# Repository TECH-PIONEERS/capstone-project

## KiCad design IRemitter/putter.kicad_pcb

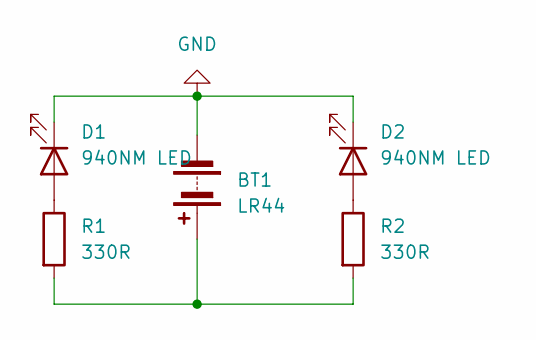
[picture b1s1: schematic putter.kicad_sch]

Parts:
BT1: LR44; batt holder
D1, D2: 940NM LED; LED_D5.0mm
R1, R2: 330R; R_Axial_DIN0207_L6.3mm_D2.5mm_P7.62mm_Horizontal

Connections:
GND: BT1.2 (-), D1.1 (K), D2.1 (K)
unnamed: BT1.1 (+), R1.2, R2.2
unnamed: D1.2 (A), R1.1
unnamed: D2.2 (A), R2.1

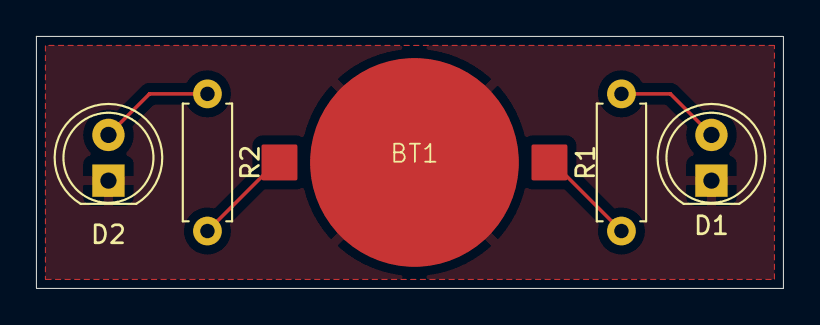
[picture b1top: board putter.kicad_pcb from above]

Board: 2 copper layers, 41.5 x 14.0 mm, 5 parts (0 on the bottom side), 4 nets.

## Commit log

2024-01-23 docs : 240109 회의록
2024-02-07 240116 회의록 - 류지수
2024-02-07 docs : 240123 회의록 - 구민성
2024-02-07 docs : 240130 회의록 - 한예지
2024-02-07 docs : 240116 회의록 - 류지수
2024-02-07 docs:주제 신청서 1차자료
2024-02-08 docs : 240207 회의록 - 박주미
2024-02-08 docs : 주제 신청 1차
2024-02-14 docs : 240214 회의록 - 류지수
2024-02-16 docs : 240216 회의록 - 박주미
2024-02-18 docs : 주제 신청 2차
2024-02-19 docs : 주제 신청 3차
2024-02-23 docs : 240222 회의록 - 류지수
2024-02-24 docs : 주제 신청 4차
2024-02-25 docs : 주제 신청 5차
2024-02-26 docs : 240225 회의록 - 박주미
2024-02-26 docs : 주제 신청 6차
2024-02-26 docs : 240226 회의록 - 한예지
2024-02-27 docs : 주제 신청 7차
2024-02-28 docs : 장애물 알림 장치 2차, 3차 신청본 삭제
2024-02-28 docs : 주제 신청 8차
2024-02-28 docs : 주제 신청 최종
2024-03-03 docs : 안전한 야간 주행을 위한 자전거, 킥보드 시스템 1차 작성
2024-03-05 docs : 시각 장애인을 위한 골프 서비스 1차 작성
2024-03-05 docs : 시각장애인을 위한 골프 시스템 1차 계획서 작성
2024-03-05 docs : 시각장애인을 위한 골프 서비스 1차 수정본
2024-03-05 docs : 공과헤드정렬
2024-03-05 docs : 공과헤드정렬 제출
2024-03-05 docs : 공과 헤드 정렬 계획서 최종본
2024-03-05 docs : 공과 헤드 정렬 계획서 최종
2024-03-05 docs : 사운드 골핑 최종
2024-03-10 docs : 퍼팅서포터 주제 신청
2024-03-10 docs : 퍼팅서포터 주제 신청서
2024-03-10 docs : [tech-pioneers]-주제 선정 보고서
2024-03-16 docs : 퍼팅서포터 주제 선정 보고서
2024-03-25 feat: 컬러 기반 공 추적 및 Canny Edge 알고리즘 결합 - 수정 필요
2024-03-25 test
2024-03-25 fix : colorLower 값 수정
2024-03-25 feat: pyttsx3, gTTS 사용 TTS 함수
2024-03-27 add : findball 주석 추가
2024-03-27 test : HoughCircles 추가해 원 검출 판별
2024-03-27 test : CannyEdge 추가
2024-03-27 comment : 할 일 추가
2024-03-27 feat : Canny Edge 추가
2024-04-01 fix : break 삭제
2024-04-01 fix : golfball_size 변수 추가
2024-04-01 fix : ZeroDivisionError 해결
2024-04-01 feat: network camera connect
2024-04-01 feat: 비프음 출력 함수를 쓰레드로 구현 및 테스트 완료
2024-04-09 바닥판 디렉토리 생성
2024-04-17 feat: crop video and add fucn(1px to 1mm)
2024-04-17 feat: add 수선의 발 코드
2024-05-01 feat: camera calibration
2024-05-01 feat: test-camera picamera connect
2024-05-01 feat: image
2024-05-01 feat: image2
2024-05-01 refact: camera
2024-05-01 카메라 보정 함수와 find ball 코드 합침
2024-05-01 카메라 보정 함수와 find ball 코드 합친 버전
2024-05-01 Picamera1 사용 버전 코드
2024-05-03 ball tracking with picamera
2024-05-03 Picamera v1 삭제
2024-05-03 feat: 공 외곽선이 특정 범위 벗어났을 경우 경고 문구 출력하는 코드
2024-05-03 add : IR pyserial test
2024-05-03 add : ir_result.txt
2024-05-03 feat: 공 외곽선이 특정 범위 벗어났을 경우 경고 문구와 비프음 출력하는 코드
2024-05-03 feat: findball + range detection + beep sound
2024-05-06 코드 파일 정리
2024-05-06 add : ir sensor with circle
2024-05-06 ir draw code
2024-05-06 feat: 골프공 검출
2024-05-06 add code
2024-05-06 feat: 골프공 검출 관련 코드
2024-05-06 Create ir_test_0506_2
    적외선 거리 측정을 탄젠트로 하는 코드 추가 버전
2024-05-06 yellow range changed
2024-05-06 fix : colorLower change
2024-05-06 add : goal code
2024-05-06 add : 골과 공 정렬
2024-05-06 feat: ballOutOfRangeAlert 함수에 isBallOutOfRang flag 추가
2024-05-07 add : get goal position
2024-05-08 refactor & add picam fps setting
2024-05-09 add : calibration
2024-05-09 카메라 보정 값
2024-05-09 ir draw test
2024-05-09 docs : 중간 발표 ppt
2024-05-09 docs : 중간 발표 ppt 수정
2024-05-11 findball code
2024-05-11 add : ir - findball mapping
2024-05-11 add : ir test 0511
2024-05-11 add: scale value func
2024-05-11 add : is_vaid_string
2024-05-11 add: min max value
2024-05-11 add : ir-opencv mapping
2024-05-13 feat: IR Camera1, 2를 서로 평행한 위치에 배치하여 퍼터의 가운데에 부착된 LED로 정렬 판단하는 코드
2024-05-13 feat: mapping_thread.py에 main 함수 추가
2024-05-13 feat: mapping_thread.py 원본
2024-05-13 feat: multiProcess
2024-05-13 jisu mapping
2024-05-13 feat: mapping_multiprocessing
2024-05-13 todo: multiprocessing
2024-05-14 add : mapping serial baudrate, timeout
2024-05-14 Update IRCamera.ino
    add more delay and reduced baudrate
2024-05-14 Create IRCameraBack
2024-05-14 Update IRCameraBack
2024-05-14 feat: utils pagame 수정
2024-05-14 add: calculate ball degrees
2024-05-14 add : is_valid_string
2024-05-14 add : 공 방향 전환 알고리즘
2024-05-14 add :utils is_valid_string
2024-05-14 del : unused
2024-05-14 mapping-0514-jisu
2024-05-14 fix : renaming mapping-0514.py
2024-05-14 add: 방향 코드
2024-05-14 add : ball direction
2024-05-16 add : calibration img
2024-05-16 camera calibration 값 수정(v5)
2024-05-16 add : image3
2024-05-16 camera calibration 값 수정(v6)
2024-05-16 utils 함수 수정: camera calibration 값 설정(v6)
2024-05-16 fix : circle, add calibration
2024-05-16 feat: Picam에서 BGR 출력 코드
2024-05-17 add : 5월 3주차 중간 점검 발표 자료
2024-05-17 5월 3주차 중간 점검 영상 수정
2024-05-17 feat: Picam에서 BGR 출력 코드 수정
2024-05-17 delete: HW 고정되기 이전에 수집한 Calibration 이미지들 삭제
2024-05-17 feat: TTS를 멀티 프로세스로 수행하는 코드 파일 mapping-p3-tts.py, utilsp3.py
2024-05-18 mapping code
2024-05-18 fix : utils 1023 delete
2024-05-18 IR Camera mapping
2024-05-18 add : gitignore
2024-05-18 docs: change file path
2024-05-18 add: gitignore
2024-05-18 feat: mapping-hard.py에 tts process 추가한 mapping-hard-tts.py 코드 파일
2024-05-18 TTS: 퍼터 값이 없을 경우 경고 알림
2024-05-18 mapping
2024-05-18 feat: checkt ball movement
2024-05-18 tts_flag 추가
2024-05-18 mapping-hard
2024-05-18 feat: tts manager
2024-05-18 feat: multiprocessing global variable list solved
2024-05-20 feat: multiprocessing manager 수정
2024-05-20 multiprocessing manager namespace
2024-05-20 feat: tts & jisu code 합침
2024-05-20 feat: change ball color to red
2024-05-20 multiprocessing
2024-05-20 feat: tts connect
2024-05-20 add: 헤드와 공 거리 함수 추가
2024-05-20 add : pixel to cm connect
2024-05-21 pylirc 파일
2024-05-21 add : 에지 검출 코드
2024-05-21 add: tts fix
2024-05-21 feat: fix ball_align bottom up return
2024-05-21 sound mid_beep 추가
2024-05-21 feat: add isMoving when calculate distance ball from head
2024-05-21 검은색만 마스킹
2024-05-21 feat: add import utils
2024-05-21 beep sound 추가
2024-05-21 feat: subprocess remote 코드 추가
2024-05-22 feat: remote process
2024-05-22 feat: head turn -ing
2024-05-23 feat: generate_TTS(text) 함수 추가
2024-05-23 English voice test
2024-05-23 feat: head alin
2024-05-24 add : 5월 4주차 중간 발표자료
2024-05-24 head align -ing
2024-05-24 add : 5월 4주차 중간 발표자료 수정
2024-05-24 fix : find code & utils tts 소리 변경
2024-05-24 feat: add confition
2024-05-24 ir align
2024-05-24 feat: add tts
2024-05-24 up down sound
2024-05-24 얼라인먼트 코드 업데이트
2024-05-24 얼라인먼트 업데이트
2024-05-24 code change
2024-05-24 안 쓰는 파일들 삭제
2024-05-24 head align
2024-05-24 first test code
2024-05-24 add : sound half version
2024-05-27 value_lock_code: tts_flag가 Value & Lock 사용하도록 수정한 코드
2024-05-28 request from jisu-R
2024-05-29 tts_flag -ing
2024-05-29 refactor: test_final_code
2024-05-30 feat: 공위치가 헤드 범위 밖으로 가면 경고 문구 출력하는 함수 -ing
2024-05-30 fix: order
2024-05-30 create directory IR_Asynchronous
2024-05-30 fix: order problem
2024-05-30 add : 5월 5주차 중간 발표 자료
2024-05-31 fix : pygame.mixer path error
2024-05-31 ball_shot
2024-05-31 goal
2024-05-31 refactor: distance func
2024-05-31 feat: 정렬 이후 동작 추가
2024-05-31 todo: ir y
2024-05-31 todo: ir y align
2024-06-01 refactor: 파일 구조
2024-06-01 add: dist direction
2024-06-01 fix: ball missing
2024-06-01 fix : head down , up female voice
2024-06-01 feat: change tts voice
2024-06-01 fix: 골 쳤을 때 판단
2024-06-01 fix: shot
2024-06-01 feat: 공 슛 조건 추가
2024-06-01 MSG file add
2024-06-01 update MSG
2024-06-01 feat: head position align
2024-06-01 head align beep case
2024-06-01 del: comment
2024-06-01 asdf
2024-06-01 head align case add
2024-06-01 align y axis
2024-06-01 add : lose, nice shot beep sound
2024-06-01 refactor: del comment and unused func
2024-06-01 add beep source
2024-06-01 feat: head align 기울기 sleep time 적용
2024-06-01 fix: priority problem
2024-06-01 add: cw ccw tts
2024-06-01 fix: distance
2024-06-01 add condition
2024-06-01 fix : voice once
2024-06-01 feat: test_head_align 함수 수정
2024-06-01 final code, final_code_v1
2024-06-01 todo: fix goal & wall crush case
2024-06-03 fix: tts_process add condition about shot_flag
2024-06-03 fix: goal tts
2024-06-03 docs: organize files
2024-06-03 feat: final.pt
2024-06-03 goal_x, goal_y 반경 값 정확하게 변경
2024-06-03 feat: 홀 안에서 방향이 바뀌는 경우를 위한 함수 수정
2024-06-04 fix : goal_x, goal_y 수정
2024-06-04 fix : goal_x, goal_y, x_threshold, y_threshold complete
2024-06-04 test : only straight goal
2024-06-04 fix : goal_x, y, xy threahold rollback, wall crash threshold 2.5
2024-06-04 fix : stuck on the threshold resolved
2024-06-04 fix: timer
2024-06-04 add : is_direction_chagned value
2024-06-04 feat:벽 범위에 있는 지 판단하는 코드 추가
2024-06-04 add: out of range tts
2024-06-04 feat: return_ball_direction
2024-06-04 todo: wall crush problem
2024-06-05 ball hit wall case -ing
2024-06-05 feat: temp_return_ball_direction 수정
2024-06-05 hole
2024-06-05 fix : check_movement arg
2024-06-05 공이 끝 벽에 맞고 홀로 들어오는 경우를 위해 uw 추가
2024-06-05 fix : check_movement threshold to shot_threshold
2024-06-05 last code 0605
2024-06-05 add : out of range condition
2024-06-07 request from R-jisu
2024-06-07 파일 복구
2024-06-07 feat: tts_process 벽 부딪히는 부분 + out of range 수정
2024-06-07 0607fixCode
2024-06-07 fix : up, down sound
2024-06-07 feat: add out of range half circle
2024-06-07 fix : wall-detect_threshold
2024-06-07 feat: add half circle out of range
2024-06-08 fix : 0608 final code
2024-06-08 before upload mp3 file
2024-06-10 fix : nice-shot 음원 소리 2.5배 키우기
2024-06-10 wall
2024-06-10 docs: comment
2024-06-10 feat: add out of range condition
2024-06-10 feat: head upper
2024-06-10 todo: modify threshold
2024-06-10 feat: add return ball direction when ball stop
2024-06-10 feat: final.py to prev
2024-06-10 fix: case
2024-06-10 feat: change float limit 340 to 350
2024-06-10 ball hit the wall
2024-06-10 fix : ball hit the wall
2024-06-10 feat : game lose only version
2024-06-11 temp_return_ball_direction에서 x 좌표 95 ~ 130 범위 추가
2024-06-11 BallHitTheWall 값 체크
2024-06-12 fix : goal xy threshold
2024-06-12 fianl_code.py
2024-06-14 docs : 최종 발표 자료
2024-06-14 docs : 최종 발표 대본
2024-06-14 IR camera input data fix
2024-07-02 노션 문서 업로드
